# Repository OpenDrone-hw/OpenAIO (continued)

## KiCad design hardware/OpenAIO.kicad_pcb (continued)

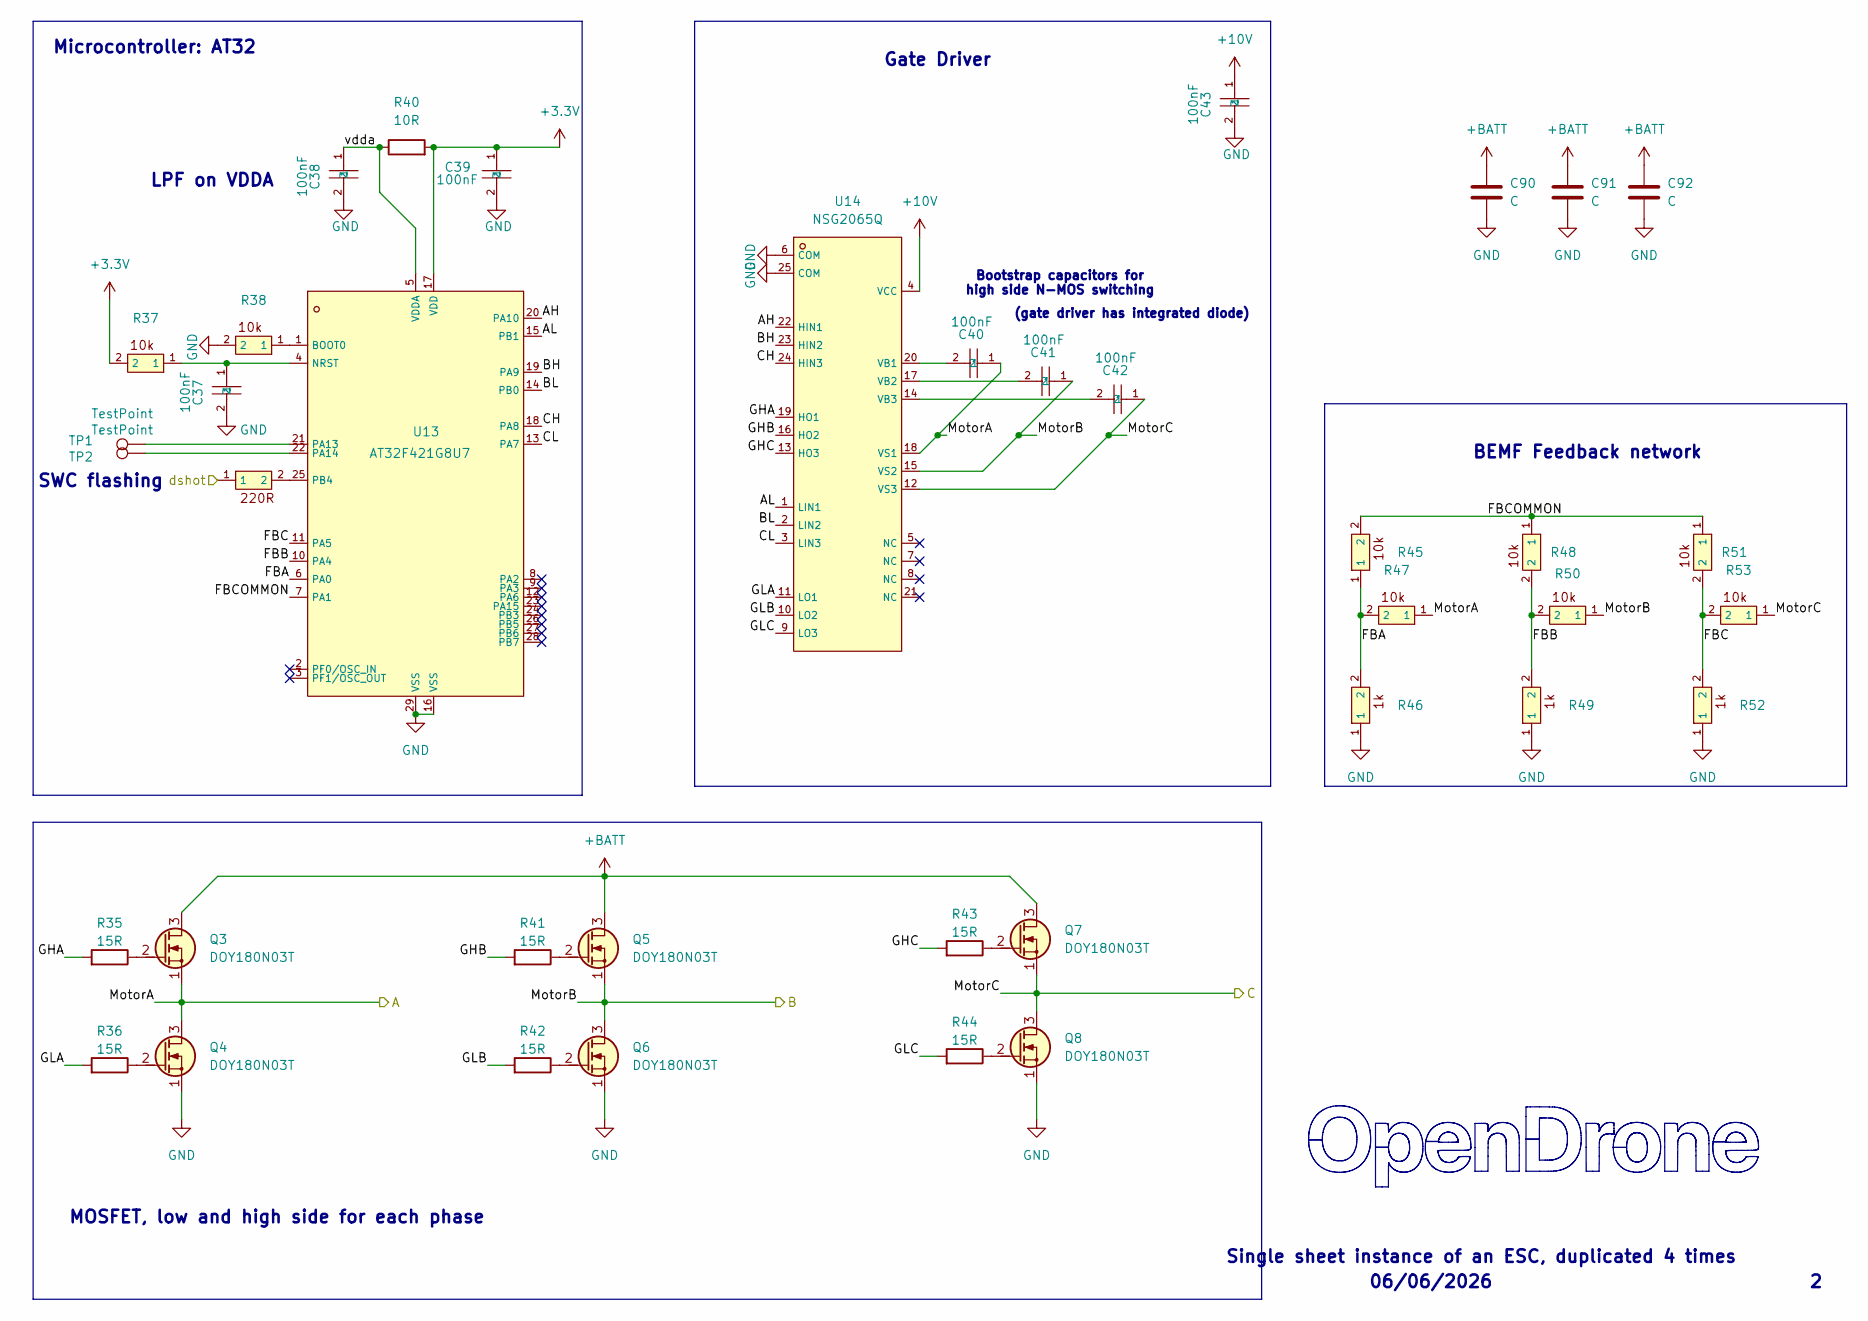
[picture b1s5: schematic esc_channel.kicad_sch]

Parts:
C37, C38, C39, C43: 100nF; C_0201_0603Metric; MPN GRM033R6YA104KE14D; LCSC C181043
C40, C41, C42: 100nF; C_0402_WIDE; MPN CL05B104KB54PNC; LCSC C307331
C90, C91, C92: C; C_0805_2012Metric
Q3, Q4, Q5, Q6, Q7, Q8: DOY180N03T; Diodes_PowerDI3333-8; MPN DOY180N03T; LCSC C49441966
R35, R36, R41, R42, R43, R44: 15R; R_0201_0603Metric; MPN 0201WMF150JTEE; LCSC C473542
R37, R38, R45, R47, R48, R50, R51, R53: 10k; R_0201_0603Metric; MPN RC0201FR-0710KL; LCSC C106225
R39: 220R; R_0201_0603Metric; MPN AC0201FR-07220RL; LCSC C226468
R40: 10R; R_0201_0603Metric; MPN RC0201FR-0710RL; LCSC C106226
R46, R49, R52: 1k; R_0201_0603Metric; MPN 0201WMF1001TEE; LCSC C270365
TP1, TP2: TestPoint; TestPoint_Pad_D1.0mm
U13: AT32F421G8U7; QFN-28_L4.0-W4.0-P0.40-TL-EP2.4; MPN AT32F421G8U7; LCSC C2765098
U14: NSG2065Q; QFN-24_L4.0-W4.0-P0.50-TL-EP2.8; MPN NSG2065Q; LCSC C41414478

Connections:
+3.3V: C39.1, R37.2, R40.2, U13.17 (VDD); also elsewhere on the board
+10V: C43.1, U14.4 (VCC); also elsewhere on the board
+BATT: C90.1, C91.1, C92.1, Q3.3 (D), Q5.3 (D), Q7.3 (D); also elsewhere on the board
/1A: C40.1, Q3.1 (S), Q4.3 (D), R47.1, U14.18 (VS1); also elsewhere on the board
/1B: C41.1, Q5.1 (S), Q6.3 (D), R50.1, U14.15 (VS2); also elsewhere on the board
/1C: C42.1, Q7.1 (S), Q8.3 (D), R53.1, U14.12 (VS3); also elsewhere on the board
/ESC1/AH: U13.20 (PA10), U14.22 (HIN1)
/ESC1/AL: U13.15 (PB1), U14.1 (LIN1)
/ESC1/BH: U13.19 (PA9), U14.23 (HIN2)
/ESC1/BL: U13.14 (PB0), U14.2 (LIN2)
/ESC1/CH: U13.18 (PA8), U14.24 (HIN3)
/ESC1/CL: U13.13 (PA7), U14.3 (LIN3)
/ESC1/FBA: R45.1, R46.2, R47.2, U13.6 (PA0)
/ESC1/FBB: R48.2, R49.2, R50.2, U13.10 (PA4)
/ESC1/FBC: R51.2, R52.2, R53.2, U13.11 (PA5)
/ESC1/FBCOMMON: R45.2, R48.1, R51.1, U13.7 (PA1)
/ESC1/GHA: R35.1, U14.19 (HO1)
/ESC1/GHB: R41.1, U14.16 (HO2)
/ESC1/GHC: R43.1, U14.13 (HO3)
/ESC1/GLA: R36.1, U14.11 (LO1)
/ESC1/GLB: R42.1, U14.10 (LO2)
/ESC1/GLC: R44.1, U14.9 (LO3)
/ESC1/vdda: C38.1, R40.1, U13.5 (VDDA)
GND: C37.2, C38.2, C39.2, C43.2, C90.2, C91.2, C92.2, Q4.1 (S), Q6.1 (S), Q8.1 (S), R38.2, R46.1, R49.1, R52.1, U13.16 (VSS), U13.29 (VSS), U14.6 (COM), U14.25 (COM); also elsewhere on the board
MOTOR1: R39.1; also elsewhere on the board
unnamed: Q3.2 (G), R35.2
unnamed: Q4.2 (G), R36.2
unnamed: Q5.2 (G), R41.2
unnamed: Q6.2 (G), R42.2
unnamed: Q7.2 (G), R43.2
unnamed: Q8.2 (G), R44.2
unnamed: R38.1, U13.1 (BOOT0)
unnamed: C37.1, R37.1, U13.4 (NRST)
unnamed: TP1.1 (1_1), U13.21 (PA13)
unnamed: TP2.1 (1_1), U13.22 (PA14)
unnamed: R39.2, U13.25 (PB4)
unnamed: C40.2, U14.20 (VB1)
unnamed: C41.2, U14.17 (VB2)
unnamed: C42.2, U14.14 (VB3)

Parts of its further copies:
C44, C45, C46, C48, C50, C51, C52, C57, C58, C60, C64: 100nF; C_0201_0603Metric; MPN GRM033R6YA104KE14D; LCSC C181043
C47, C49, C53, C54, C55, C56, C59, C61, C62, C63: 100nF; C_0402_WIDE; MPN CL05B104KB54PNC; LCSC C307331
C93, C94, C95, C96, C97, C98, C99, C100, C101: C; C_0805_2012Metric
Q9, Q10, Q11, Q12, Q13, Q14, Q15, Q16, Q17, Q18, Q19, Q20, Q21, Q22, Q23, Q24, Q25, Q26: DOY180N03T; Diodes_PowerDI3333-8; MPN DOY180N03T; LCSC C49441966
R55, R60, R61, R62, R63, R73, R79, R80, R81, R82, R92, R93, R98, R99, R100, R101: 15R; R_0201_0603Metric; MPN 0201WMF150JTEE; LCSC C473542
R56, R57, R64, R66, R67, R69, R70, R72, R75, R83, R85, R86, R88, R89, R91, R94, R95, R102, R104, R105, R107, R108, R110: 10k; R_0201_0603Metric; MPN RC0201FR-0710KL; LCSC C106225
R58, R77, R96: 220R; R_0201_0603Metric; MPN AC0201FR-07220RL; LCSC C226468
R65, R68, R71, R84, R87, R90, R103, R106, R109: 1k; R_0201_0603Metric; MPN 0201WMF1001TEE; LCSC C270365
R78, R97: 10R; R_0201_0603Metric; MPN RC0201FR-0710RL; LCSC C106226
TP3, TP4, TP5, TP6, TP7, TP8: TestPoint; TestPoint_Pad_D1.0mm
U15, U17, U19: AT32F421G8U7; QFN-28_L4.0-W4.0-P0.40-TL-EP2.4; MPN AT32F421G8U7; LCSC C2765098
U16, U18, U20: NSG2065Q; QFN-24_L4.0-W4.0-P0.50-TL-EP2.8; MPN NSG2065Q; LCSC C41414478

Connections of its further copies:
+3.3V: C46.1, C53.1, C60.1, R56.2, R75.2, R78.2, R94.2, R97.2, U15.17 (VDD), U17.17 (VDD), U19.17 (VDD); also elsewhere on the board
+10V: C50.1, C57.1, C64.1, U16.4 (VCC), U18.4 (VCC), U20.4 (VCC); also elsewhere on the board
+BATT: C93.1, C94.1, C95.1, C96.1, C97.1, C98.1, C99.1, C100.1, C101.1, Q9.3 (D), Q11.3 (D), Q13.3 (D), Q15.3 (D), Q17.3 (D), Q19.3 (D), Q21.3 (D), Q23.3 (D), Q25.3 (D); also elsewhere on the board
/2A: C47.1, Q9.1 (S), Q10.3 (D), R66.1, U16.18 (VS1); also elsewhere on the board
/2B: C48.1, Q11.1 (S), Q12.3 (D), R69.1, U16.15 (VS2); also elsewhere on the board
/2C: C49.1, Q13.1 (S), Q14.3 (D), R72.1, U16.12 (VS3); also elsewhere on the board
/3A: C54.1, Q15.1 (S), Q16.3 (D), R85.1, U18.18 (VS1); also elsewhere on the board
/3B: C55.1, Q17.1 (S), Q18.3 (D), R88.1, U18.15 (VS2); also elsewhere on the board
/3C: C56.1, Q19.1 (S), Q20.3 (D), R91.1, U18.12 (VS3); also elsewhere on the board
/4A: C61.1, Q21.1 (S), Q22.3 (D), R104.1, U20.18 (VS1); also elsewhere on the board
/4B: C62.1, Q23.1 (S), Q24.3 (D), R107.1, U20.15 (VS2); also elsewhere on the board
/4C: C63.1, Q25.1 (S), Q26.3 (D), R110.1, U20.12 (VS3); also elsewhere on the board
/ESC2/AH: U15.20 (PA10), U16.22 (HIN1)
/ESC2/AL: U15.15 (PB1), U16.1 (LIN1)
/ESC2/BH: U15.19 (PA9), U16.23 (HIN2)
/ESC2/BL: U15.14 (PB0), U16.2 (LIN2)
/ESC2/CH: U15.18 (PA8), U16.24 (HIN3)
/ESC2/CL: U15.13 (PA7), U16.3 (LIN3)
/ESC2/FBA: R64.1, R65.2, R66.2, U15.6 (PA0)
/ESC2/FBB: R67.2, R68.2, R69.2, U15.10 (PA4)
/ESC2/FBC: R70.2, R71.2, R72.2, U15.11 (PA5)
/ESC2/FBCOMMON: R64.2, R67.1, R70.1, U15.7 (PA1)
/ESC2/GHA: U16.19 (HO1); also elsewhere on the board
/ESC2/GHB: R60.1, U16.16 (HO2)
/ESC2/GHC: R62.1, U16.13 (HO3)
/ESC2/GLA: R55.1, U16.11 (LO1)
/ESC2/GLB: R61.1, U16.10 (LO2)
/ESC2/GLC: R63.1, U16.9 (LO3)
/ESC2/vdda: C45.1, U15.5 (VDDA); also elsewhere on the board
/ESC3/AH: U17.20 (PA10), U18.22 (HIN1)
/ESC3/AL: U17.15 (PB1), U18.1 (LIN1)
/ESC3/BH: U17.19 (PA9), U18.23 (HIN2)
/ESC3/BL: U17.14 (PB0), U18.2 (LIN2)
/ESC3/CH: U17.18 (PA8), U18.24 (HIN3)
/ESC3/CL: U17.13 (PA7), U18.3 (LIN3)
/ESC3/FBA: R83.1, R84.2, R85.2, U17.6 (PA0)
/ESC3/FBB: R86.2, R87.2, R88.2, U17.10 (PA4)
/ESC3/FBC: R89.2, R90.2, R91.2, U17.11 (PA5)
/ESC3/FBCOMMON: R83.2, R86.1, R89.1, U17.7 (PA1)
/ESC3/GHA: R73.1, U18.19 (HO1)
/ESC3/GHB: R79.1, U18.16 (HO2)
/ESC3/GHC: R81.1, U18.13 (HO3)
/ESC3/GLA: U18.11 (LO1); also elsewhere on the board
/ESC3/GLB: R80.1, U18.10 (LO2)
/ESC3/GLC: R82.1, U18.9 (LO3)
/ESC3/vdda: C52.1, R78.1, U17.5 (VDDA)
/ESC4/AH: U19.20 (PA10), U20.22 (HIN1)
/ESC4/AL: U19.15 (PB1), U20.1 (LIN1)
/ESC4/BH: U19.19 (PA9), U20.23 (HIN2)
/ESC4/BL: U19.14 (PB0), U20.2 (LIN2)
/ESC4/CH: U19.18 (PA8), U20.24 (HIN3)
/ESC4/CL: U19.13 (PA7), U20.3 (LIN3)
/ESC4/FBA: R102.1, R103.2, R104.2, U19.6 (PA0)
/ESC4/FBB: R105.2, R106.2, R107.2, U19.10 (PA4)
/ESC4/FBC: R108.2, R109.2, R110.2, U19.11 (PA5)
/ESC4/FBCOMMON: R102.2, R105.1, R108.1, U19.7 (PA1)
/ESC4/GHA: R92.1, U20.19 (HO1)
/ESC4/GHB: R98.1, U20.16 (HO2)
/ESC4/GHC: R100.1, U20.13 (HO3)
/ESC4/GLA: R93.1, U20.11 (LO1)
/ESC4/GLB: R99.1, U20.10 (LO2)
/ESC4/GLC: R101.1, U20.9 (LO3)
/ESC4/vdda: C59.1, R97.1, U19.5 (VDDA)
GND: C44.2, C45.2, C46.2, C50.2, C51.2, C52.2, C53.2, C57.2, C58.2, C59.2, C60.2, C64.2, C93.2, C94.2, C95.2, C96.2, C97.2, C98.2, C99.2, C100.2, C101.2, Q10.1 (S), Q12.1 (S), Q14.1 (S), Q16.1 (S), Q18.1 (S), Q20.1 (S), Q22.1 (S), Q24.1 (S), Q26.1 (S), R57.2, R65.1, R68.1, R71.1, R84.1, R87.1, R90.1, R95.2, R103.1, R106.1, R109.1, U15.16 (VSS), U15.29 (VSS), U16.6 (COM), U16.25 (COM), U17.16 (VSS), U17.29 (VSS), U18.6 (COM), U18.25 (COM), U19.16 (VSS), U19.29 (VSS), U20.6 (COM), U20.25 (COM); also elsewhere on the board
MOTOR2: R58.1; also elsewhere on the board
MOTOR3: R77.1; also elsewhere on the board
MOTOR4: R96.1; also elsewhere on the board
unnamed 154: Q9.2 (G); also elsewhere on the board
unnamed: Q10.2 (G), R55.2
unnamed: Q11.2 (G), R60.2
unnamed: Q12.2 (G), R61.2
unnamed: Q13.2 (G), R62.2
unnamed: Q14.2 (G), R63.2
unnamed: Q15.2 (G), R73.2
unnamed 161: Q16.2 (G); also elsewhere on the board
unnamed: Q17.2 (G), R79.2
unnamed: Q18.2 (G), R80.2
unnamed: Q19.2 (G), R81.2
unnamed: Q20.2 (G), R82.2
unnamed: Q21.2 (G), R92.2
unnamed: Q22.2 (G), R93.2
unnamed: Q23.2 (G), R98.2
unnamed: Q24.2 (G), R99.2
unnamed: Q25.2 (G), R100.2
unnamed: Q26.2 (G), R101.2
unnamed: R57.1, U15.1 (BOOT0)
unnamed: C44.1, R56.1, U15.4 (NRST)
unnamed: TP3.1 (1_1), U15.21 (PA13)
unnamed: TP4.1 (1_1), U15.22 (PA14)
unnamed: R58.2, U15.25 (PB4)
unnamed: C47.2, U16.20 (VB1)
unnamed: C48.2, U16.17 (VB2)
unnamed: C49.2, U16.14 (VB3)
unnamed 204: U17.1 (BOOT0); also elsewhere on the board
unnamed: C51.1, R75.1, U17.4 (NRST)
unnamed: TP5.1 (1_1), U17.21 (PA13)
unnamed: TP6.1 (1_1), U17.22 (PA14)
unnamed: R77.2, U17.25 (PB4)
unnamed: C54.2, U18.20 (VB1)
unnamed: C55.2, U18.17 (VB2)
unnamed: C56.2, U18.14 (VB3)
unnamed: R95.1, U19.1 (BOOT0)
unnamed: C58.1, R94.1, U19.4 (NRST)
unnamed: TP7.1 (1_1), U19.21 (PA13)
unnamed: TP8.1 (1_1), U19.22 (PA14)
unnamed: R96.2, U19.25 (PB4)
unnamed: C61.2, U20.20 (VB1)
unnamed: C62.2, U20.17 (VB2)
unnamed: C63.2, U20.14 (VB3)

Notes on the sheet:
Bootstrap capacitors for high side N-MOS switching
Gate Driver
MOSFET, low and high side for each phase
Single sheet instance of an ESC, duplicated 4 times
Microcontroller: AT32
SWC flashing
(gate driver has integrated diode)
06/06/2026
BEMF Feedback network
LPF on VDDA

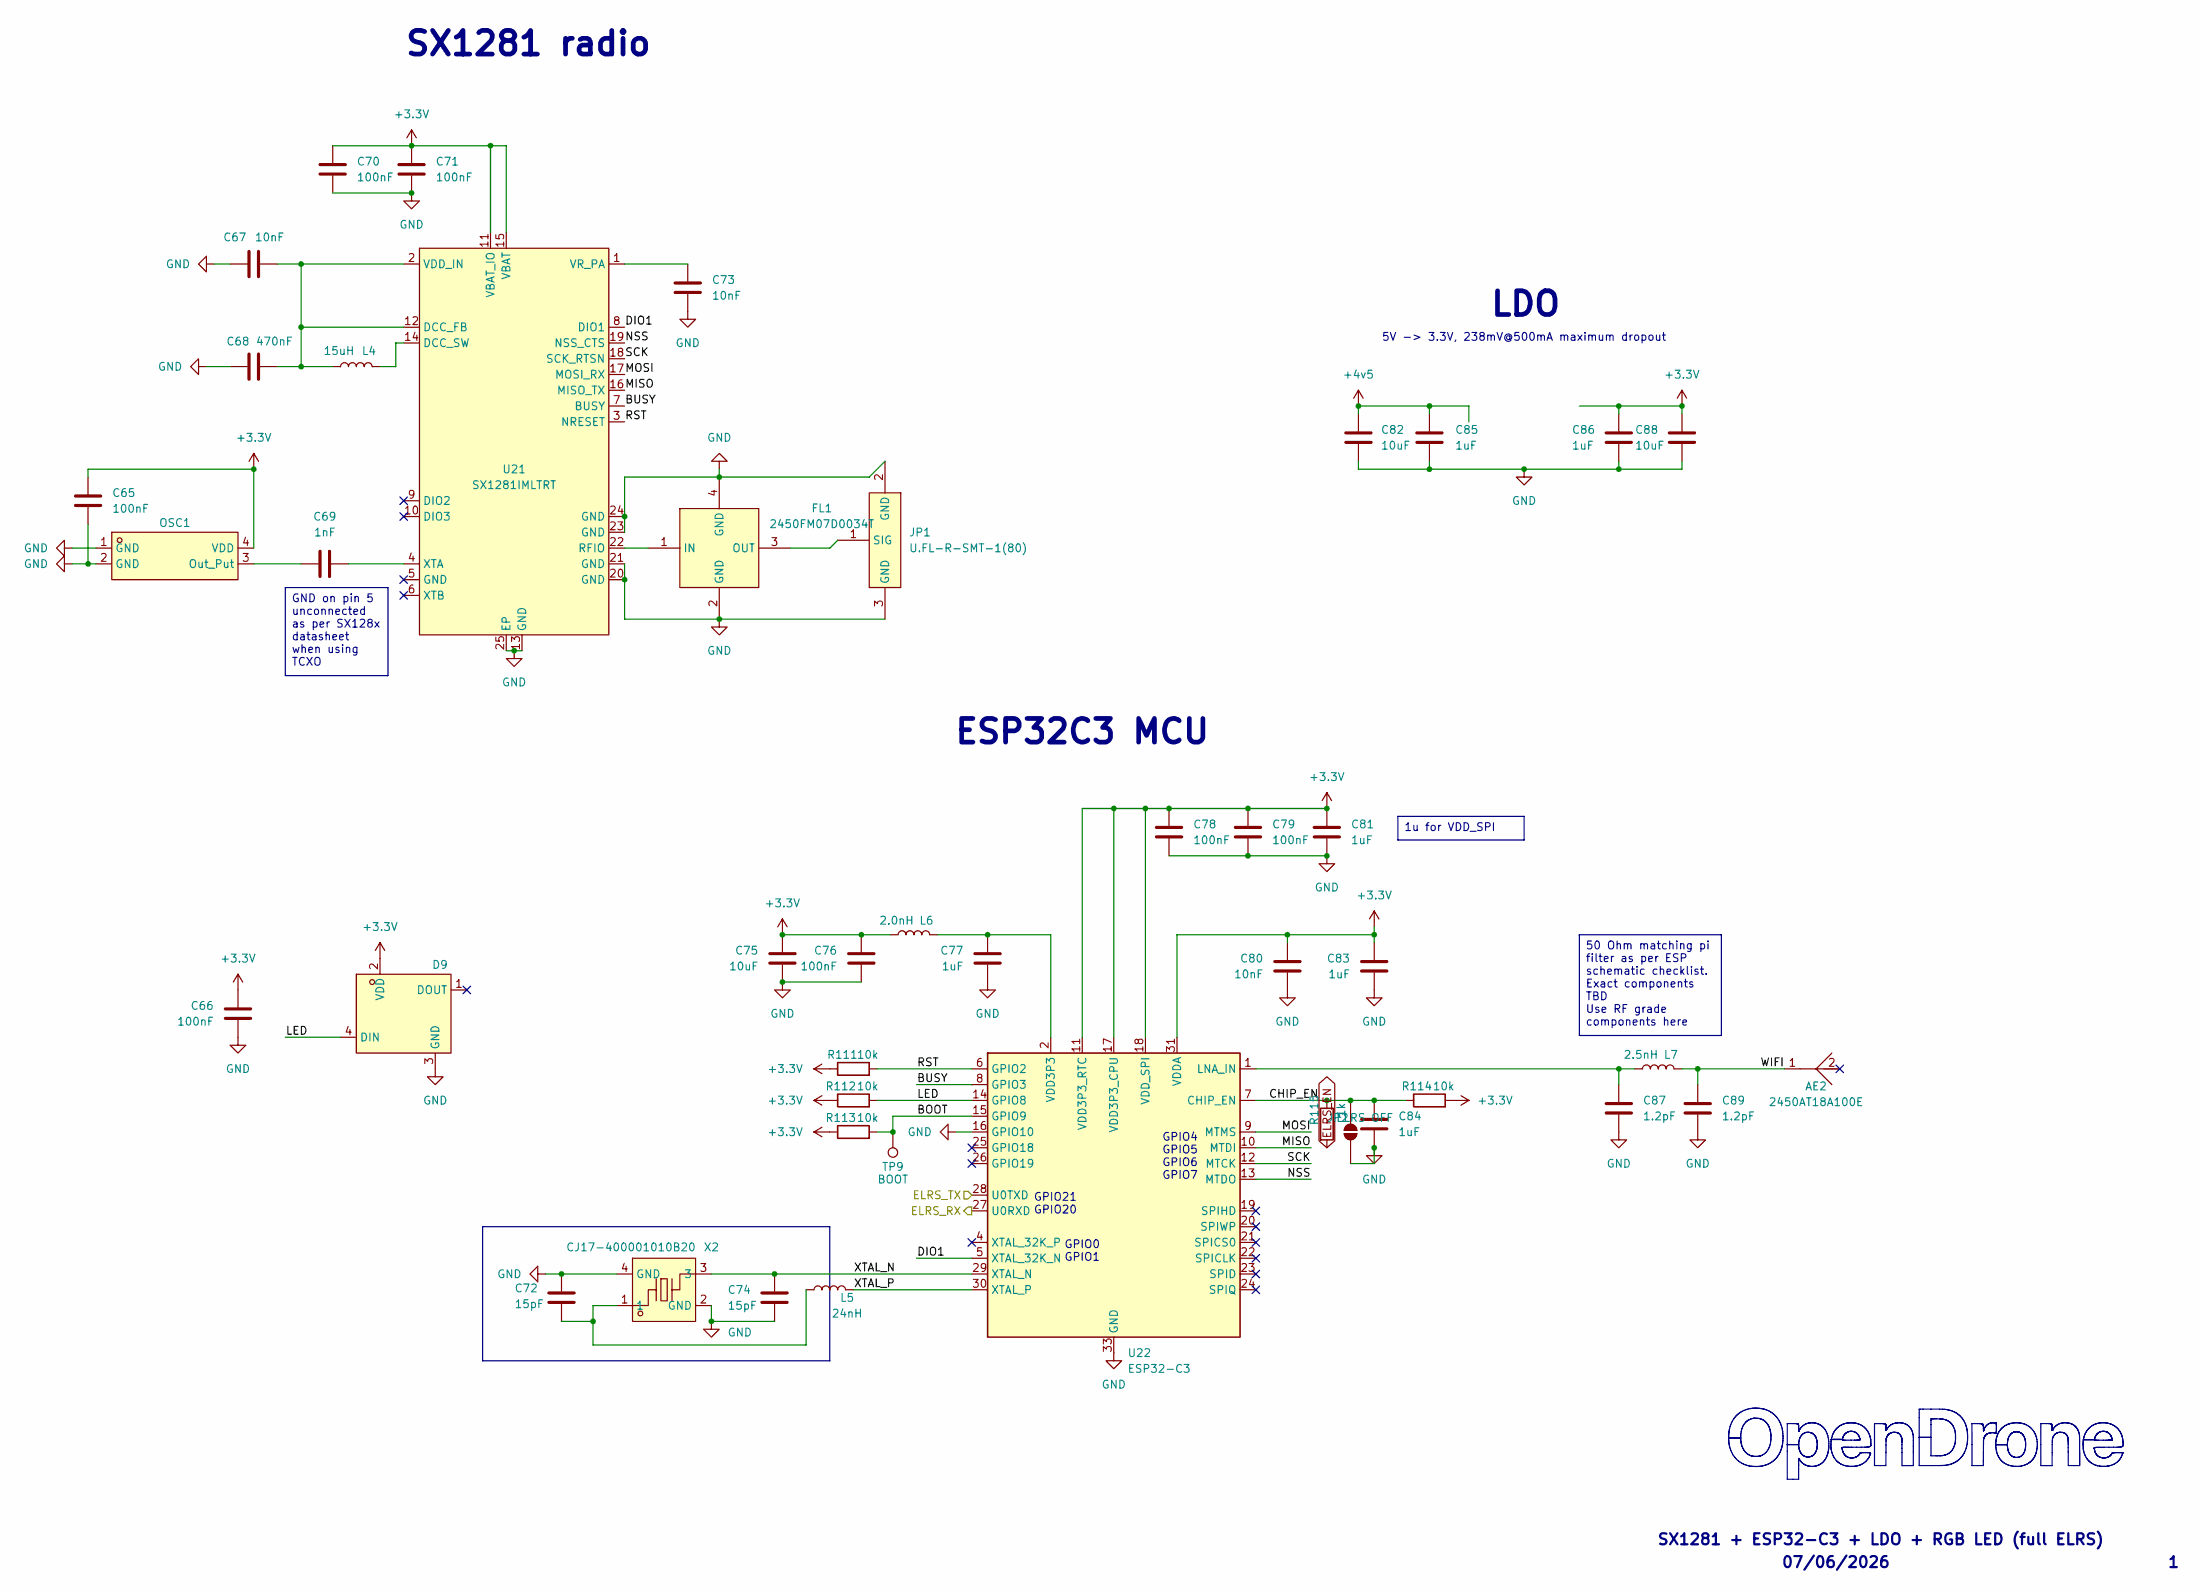
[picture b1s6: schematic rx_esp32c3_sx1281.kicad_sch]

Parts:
AE2: 2450AT18A100E; ANT-SMD_L3.2-W1.6; LCSC Part C89334
C65, C66, C70, C71, C76, C78, C79: 100nF; C_0201_0603Metric; LCSC C76939
C67, C73, C80: 10nF; C_0201_0603Metric; LCSC C2168164
C68: 470nF; C_0201_0603Metric; LCSC C85926
C69: 1nF; C_0201_0603Metric; LCSC C66942
C72, C74: 15pF; C_0201_0603Metric; LCSC C85891
C75: 10uF; C_0402_1005Metric; LCSC C76991
C77, C81, C83, C84, C85, C86: 1uF; C_0201_0603Metric; LCSC C76935
C82, C88: 10uF; C_0402_1005Metric; LCSC C15525
C87, C89: 1.2pF; C_0201_0603Metric; LCSC C85895
D9: XL-1010RGBC-WS2812B; LED-SMD_4P-L1.0-W1.0-TL_XL-1010RGBC-WS2812B; LCSC Part C5349953
FL1: 2450FM07D0034T; FILTER-SMD_4P-L1.0-W0.5-L; MPN 2450FM07D0034T; LCSC Part C2651081
JP1: U.FL-R-SMT-1(80); RF-SMD_FRF05002-JSS103M; LCSC Part C88374
JP2: ELRS OFF; SolderJumper-2_P0.65mm_Tiny_Open
L4: 15uH; L_0805_2012Metric
L5: 24nH; L_0201_0603Metric; LCSC C206441
L6: 2.0nH; L_0201_0603Metric; LCSC C86125
L7: 2.5nH; L_0201_0603Metric; LCSC C206435
OSC1: OW7EL89CENUNFAYLC-52M; OSC-SMD_4P-L2.0-W1.6-BL_TXC_7Z; LCSC Part C22434896
R111, R112, R113, R114: 10k; R_0201_0603Metric; LCSC C106225
R115: 1k; R_0201_0603Metric
TP9: BOOT; SolderPad_1.2x2.0mm
U21: SX1281IMLTRT; QFN-24_L4.0-W4.0-P0.50-TL-EP2.6; LCSC Part C2151551
U22: ESP32-C3; QFN-32-1EP_5x5mm_P0.5mm_EP3.7x3.7mm
X2: CJ17-400001010B20; CRYSTAL-SMD_4P-L1.6-W1.2-BL; LCSC Part C2875272

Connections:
+3.3V: C65.1, C66.1, C70.1, C71.1, C75.1, C76.1, C78.1, C79.1, C80.1, C81.1, C83.1, C86.1, C88.1, D9.2 (VDD), L6.2, OSC1.4 (VDD), R111.1, R112.1, R113.1, R114.2, U21.11 (VBAT_IO), U21.15 (VBAT), U22.11 (VDD3P3_RTC), U22.17 (VDD3P3_CPU), U22.18 (VDD_SPI), U22.31 (VDDA), U22.32 (VDDA); also elsewhere on the board
+4v5: C82.1, C85.1; also elsewhere on the board
/RX/BOOT: R113.2, TP9.1 (1_1), U22.15 (GPIO9)
/RX/BUSY: U21.7 (BUSY), U22.8 (GPIO3)
/RX/CHIP_EN: C84.1, JP2.2 (B), R114.1, R115.1, U22.7 (CHIP_EN)
/RX/DIO1: U21.8 (DIO1), U22.5 (XTAL_32K_N)
/RX/LED: D9.4 (DIN), R112.2, U22.14 (GPIO8)
/RX/MISO: U21.16 (MISO_TX), U22.10 (MTDI)
/RX/MOSI: U21.17 (MOSI_RX), U22.9 (MTMS)
/RX/NSS: U21.19 (NSS_CTS), U22.13 (MTDO)
/RX/RST: R111.2, U21.3 (NRESET), U22.6 (GPIO2)
/RX/SCK: U21.18 (SCK_RTSN), U22.12 (MTCK)
/RX/WIFI: AE2.1, C89.1, L7.1
/RX/XTAL_N: C74.1, U22.29 (XTAL_N), X2.3
/RX/XTAL_P: L5.2, U22.30 (XTAL_P)
ELRS_EN: R115.2; also elsewhere on the board
GND: C65.2, C66.2, C67.1, C68.1, C70.2, C71.2, C72.2, C73.2, C74.2, C75.2, C76.2, C77.2, C78.2, C79.2, C80.2, C81.2, C82.2, C83.2, C84.2, C85.2, C86.2, C87.2, C88.2, C89.2, D9.3 (GND), FL1.2 (GND), FL1.4 (GND), JP1.2 (GND), JP1.3 (GND), JP2.1 (A), OSC1.1 (GND), OSC1.2 (GND), U21.13 (GND), U21.20 (GND), U21.21 (GND), U21.23 (GND), U21.24 (GND), U21.25 (EP), U22.16 (GPIO10), U22.33 (GND), X2.2 (GND), X2.4 (GND); also elsewhere on the board
unnamed: C72.1, L5.1, X2.1
unnamed: C77.1, L6.1, U22.2 (VDD3P3), U22.3 (VDD3P3)
unnamed: FL1.1 (IN), U21.22 (RFIO)
unnamed: FL1.3 (OUT), JP1.1 (SIG)
unnamed: C69.1, OSC1.3 (Out_Put)
unnamed: C67.2, C68.2, L4.1, U21.2 (VDD_IN), U21.12 (DCC_FB)
unnamed: L4.2, U21.14 (DCC_SW)
unnamed: C73.1, U21.1 (VR_PA)
unnamed: C69.2, U21.4 (XTA)
unnamed: C87.1, L7.2, U22.1 (LNA_IN)
UART1_RX: U22.28 (U0TXD); also elsewhere on the board
UART1_TX: U22.27 (U0RXD); also elsewhere on the board

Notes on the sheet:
5V -> 3.3V, 238mV@500mA maximum dropout
GPIO0 GPIO1
SX1281 + ESP32-C3 + LDO + RGB LED (full ELRS)
GPIO21 GPIO20
GPIO4 GPIO5 GPIO6 GPIO7
SX1281 radio
LDO
ESP32C3 MCU
07/06/2026
GND on pin 5 unconnected as per SX128x datasheet when using TCXO
1u for VDD_SPI
50 Ohm matching pi filter as per ESP schematic checklist. Exact components TBD Use RF grade components here

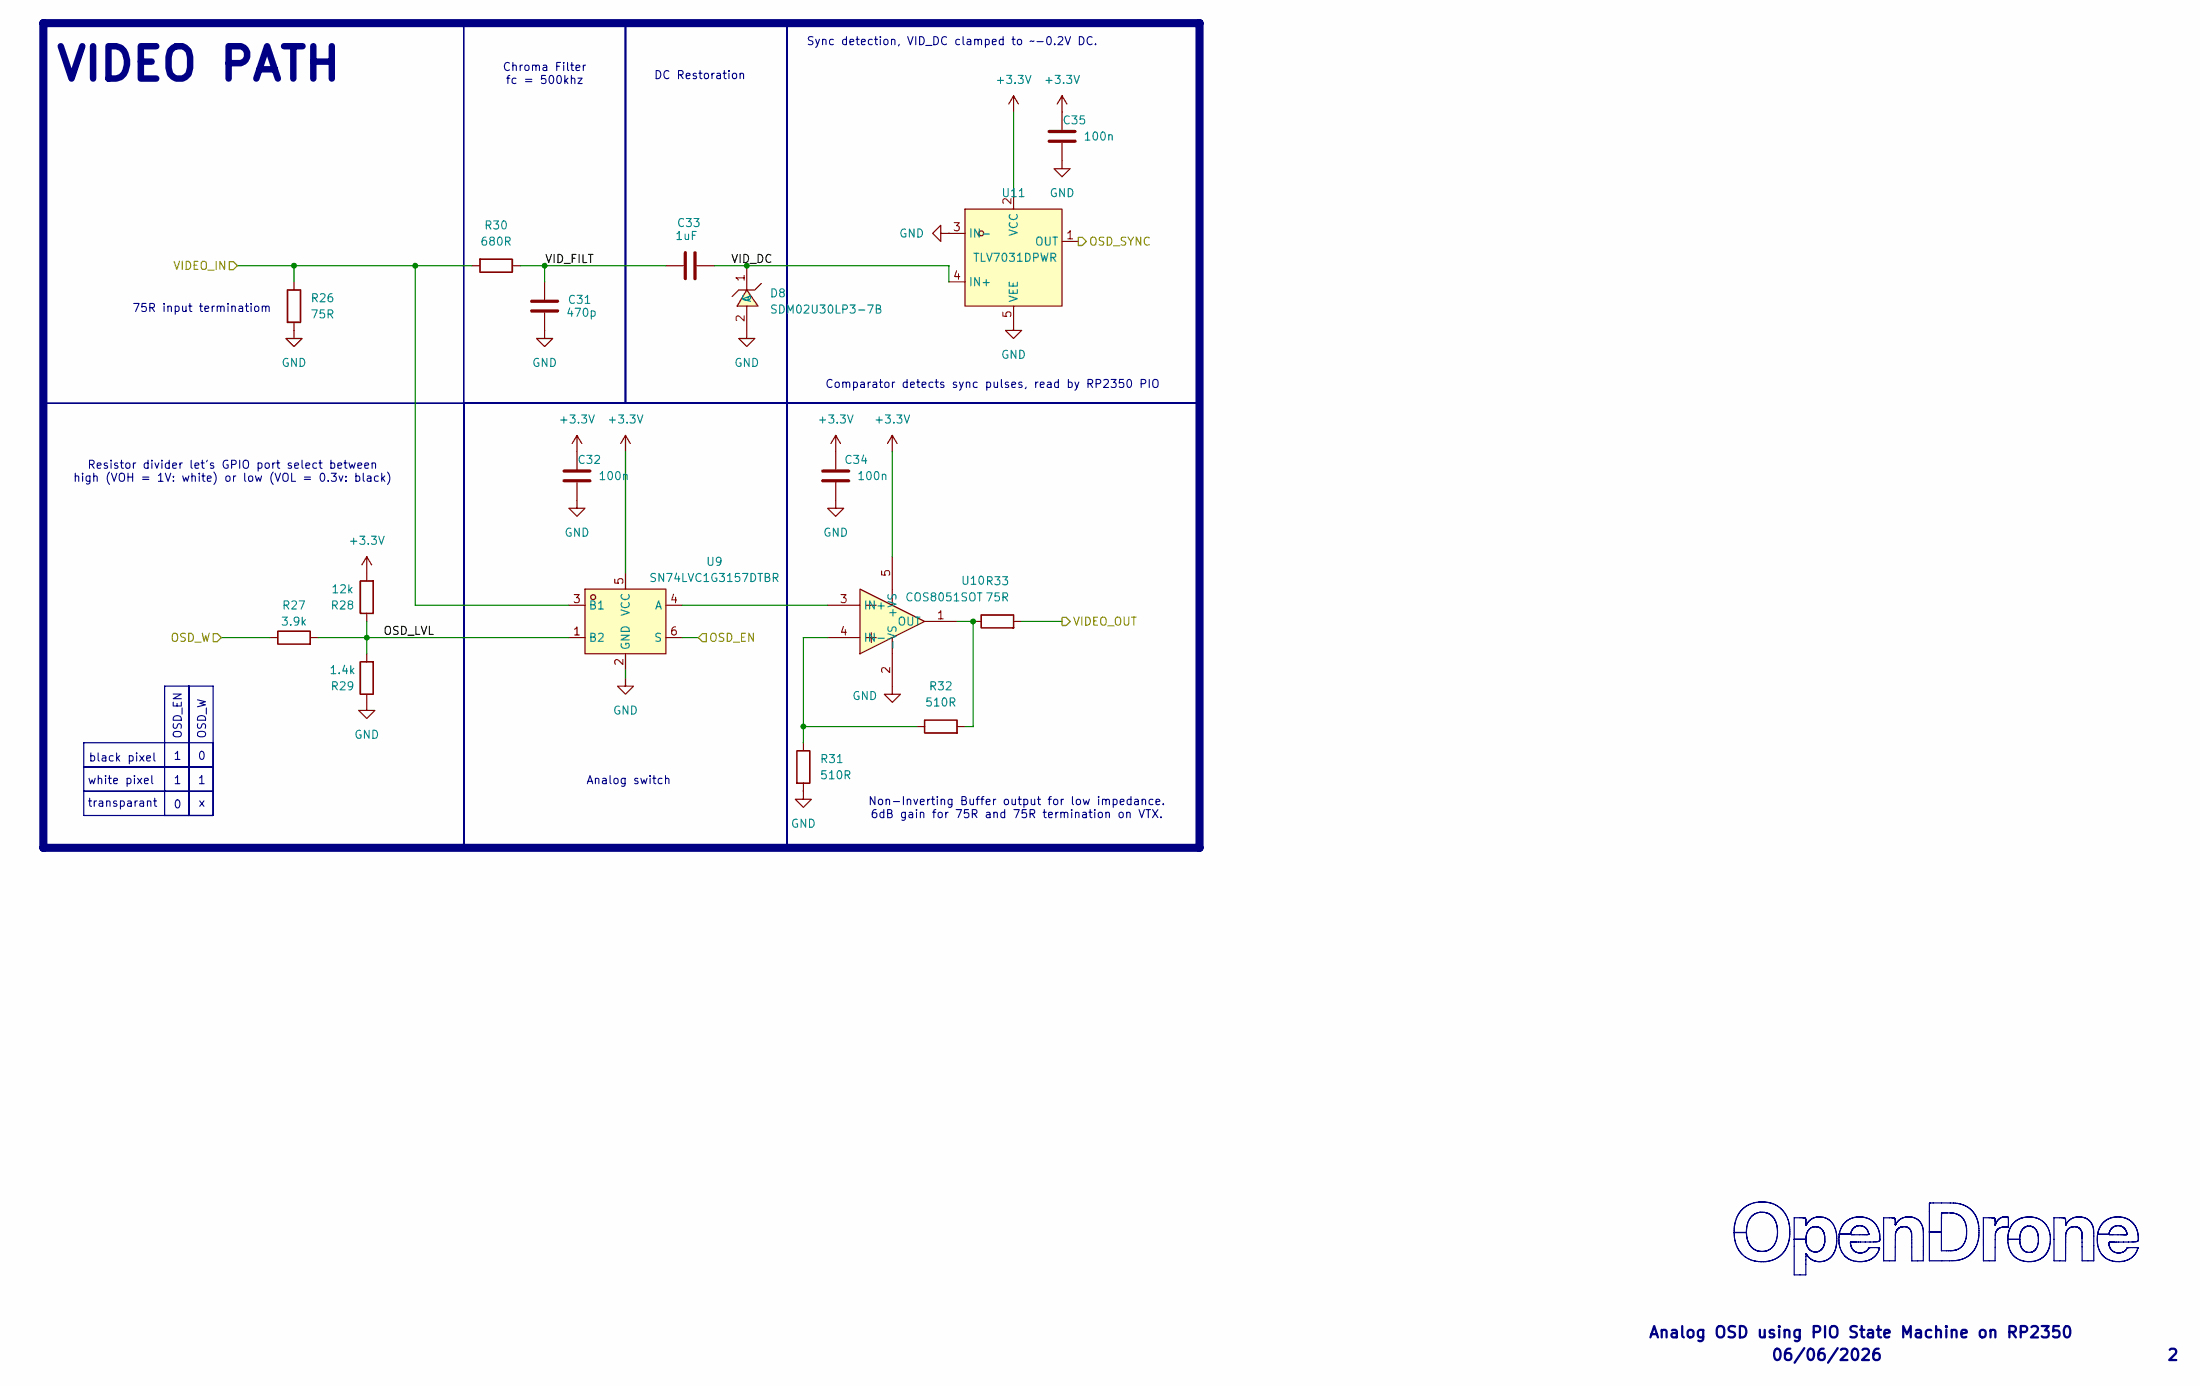
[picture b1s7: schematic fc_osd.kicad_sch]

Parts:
C31: 470p; C_0201_0603Metric; MPN CC0201JRX7R9BB471; LCSC C526944
C32, C34, C35: 100n; C_0201_0603Metric; MPN GRM033R60J104KE19D; LCSC C76928
C33: 1uF; C_0402_1005Metric; MPN CL05A105KA5NQNC; LCSC C52923
D8: SDM02U30LP3-7B; X3-DFN0603-2_L0.6-W0.3-RD; MPN SDM02U30LP3-7B; LCSC C151629
R26, R33: 75R; R_0201_0603Metric; MPN RC0201FR-0775RL; LCSC C274878
R27: 3.9k; R_0201_0603Metric; MPN RC0201FR-073K9L; LCSC C273280
R28: 12k; R_0201_0603Metric; MPN 0201WMF1202TEE; LCSC C270363
R29: 1.4k; R_0201_0603Metric; MPN 0201WMF1401TEE; LCSC C423739
R30: 680R; R_0201_0603Metric; MPN 0201WMF6800TEE; LCSC C473509
R31, R32: 510R; R_0201_0603Metric; LCSC C57784
U9: SN74LVC1G3157DTBR; X2SON-6_L1.0-W0.8-BL; MPN SN74LVC1G3157DTBR; LCSC C2673087
U10: COS8051SOT; SOT-23-5_L3.0-W1.7-P0.95-LS2.8-BR; MPN COS8051SOT; LCSC C7463385
U11: TLV7031DPWR; X2SON-4_L0.8-W0.8-P0.48-TL-A; MPN TLV7031DPWR; LCSC C2876045

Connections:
+3.3V: C32.1, C34.1, C35.1, R28.2, U9.5 (VCC), U10.5 (+VS), U11.2 (VCC); also elsewhere on the board
/OSD/OSD_EN: U9.6 (S); also elsewhere on the board
/OSD/OSD_LVL: R27.2, R28.1, R29.2, U9.1 (B2)
/OSD/OSD_SYNC: U11.1 (OUT); also elsewhere on the board
/OSD/OSD_W: R27.1; also elsewhere on the board
/OSD/VIDEO_IN: R26.1, R30.2, U9.3 (B1); also elsewhere on the board
/OSD/VIDEO_OUT: R33.2; also elsewhere on the board
/OSD/VID_DC: C33.2, D8.1 (C), U11.4 (IN+)
/OSD/VID_FILT: C31.1, C33.1, R30.1
GND: C31.2, C32.2, C34.2, C35.2, D8.2 (A), R26.2, R29.1, R31.2, U9.2 (GND), U10.2 (-VS), U11.3 (IN-), U11.5 (VEE); also elsewhere on the board
unnamed: U9.4 (A), U10.3 (IN+)
unnamed: R31.1, R32.1, U10.4 (IN-)
unnamed: R32.2, R33.1, U10.1 (OUT)

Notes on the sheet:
Sync detection, VID_DC clamped to ~-0.2V DC.
Non-Inverting Buffer output for low impedance. 6dB gain for 75R and 75R termination on VTX.
VIDEO PATH
06/06/2026
Analog switch
black pixel
white pixel
OSD_W
75R input terminatiom
Resistor divider let's GPIO port select between high (VOH = 1V: white) or low (VOL = 0.3v: black)
DC Restoration
Chroma Filter fc = 500khz
OSD_EN
transparant
Analog OSD using PIO State Machine on RP2350
Comparator detects sync pulses, read by RP2350 PIO

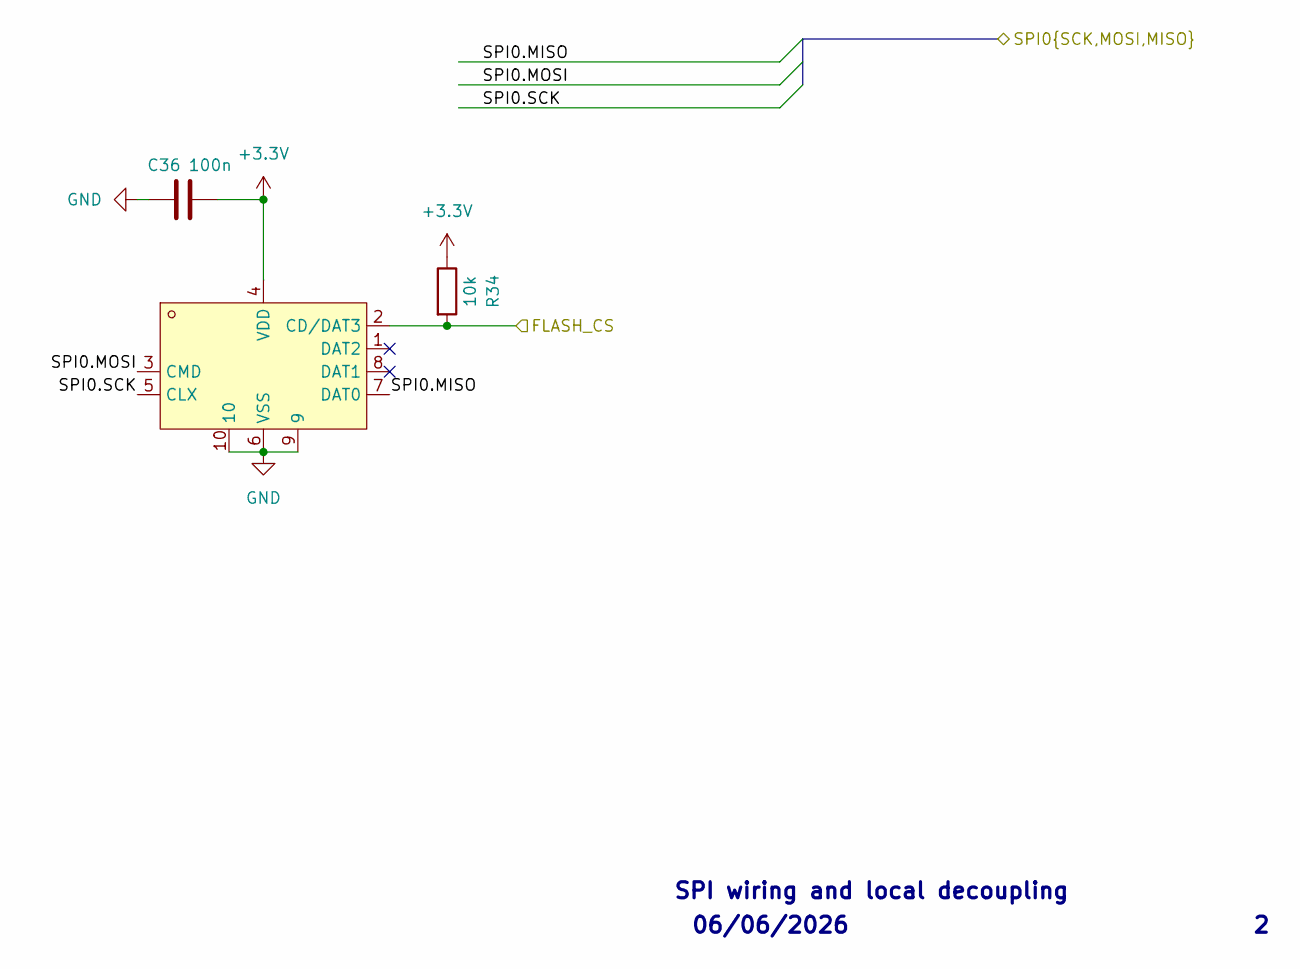
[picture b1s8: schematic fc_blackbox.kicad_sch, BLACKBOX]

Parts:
C36: 100n; C_0201_0603Metric; MPN GRM033R61E104KE14D; LCSC C76939
Card1: TF-021B-H265; TF-SMD_TF-021B-H265; LCSC C498185
R34: 10k; R_0201_0603Metric; MPN RC0201FR-0710KL; LCSC C106225

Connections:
+3.3V: C36.1, Card1.4 (VDD), R34.1; also elsewhere on the board
FLASH_CS: Card1.2 (CD/DAT3), R34.2; also elsewhere on the board
GND: C36.2, Card1.6 (VSS), Card1.9, Card1.10; also elsewhere on the board
SPI0.MISO: Card1.7 (DAT0); also elsewhere on the board
SPI0.MOSI: Card1.3 (CMD); also elsewhere on the board
SPI0.SCK: Card1.5 (CLX); also elsewhere on the board

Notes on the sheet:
SPI wiring and local decoupling
06/06/2026

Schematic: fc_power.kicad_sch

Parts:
C18, C19: 4.7uF 50v; C_0805_2012Metric; MPN CL21A475KBQNNNE; LCSC C98192
C20, C21, C26: 100n; C_0201_0603Metric; MPN GRM033R61E104KE14D; LCSC C76939
C23, C24: 22uF; C_0603_1608Metric; MPN CL10A226MO7JZNC; LCSC C2762594
C25: 4.7uF; C_0402_1005Metric; MPN CL05A475MP5NRNC; LCSC C23733
C27, C28: 22uF; C_0402_1005Metric; MPN GRM155R60J226ME11D; LCSC C415703
C102, C103: C; C_0805_2012Metric
C105, C106: C; C_1206_3216Metric
D2, D3: DSK24; SOD-123_L2.8-W1.8-LS3.7-RD; MPN DSK24; LCSC C64890
D4, D5, D6, D7: LED_1_Green; LED_0402_1005Metric; MPN XL-1005UGC; LCSC C965793
L2, L3: XRTC303020D4R7MBCA; IND-SMD_L3.0-W3.0_AFE303020S; MPN XRTC303020D4R7MBCA; LCSC C39846837
R17, R19: 100k; R_0201_0603Metric; MPN 0201WMF1003TEE; LCSC C270364
R18, R23: 6.49k; R_0201_0603Metric; LCSC C2107920
R20: 13.7k; R_0201_0603Metric; MPN RC-01W1372FT; LCSC C320695
R21: 7.5k; R_0201_0603Metric; LCSC C474437
R22: 2.4k; R_0201_0603Metric; LCSC C166281
R24: 510R; R_0201_0603Metric; LCSC C57784
TP30: TestPoint; TestPoint_Pad_D1.0mm
U3, U4: LMR51430YFDDCR; SOT-23-6_L2.9-W1.6-P0.95-LS2.9-BL; MPN LMR51430YFDDCR; LCSC C5219261
U6: LP5912-1.8DRVR; WSON-6-1EP_2x2mm_P0.65mm_EP1x1.6mm_ThermalVias; MPN LP5912-1.8DRVR; LCSC C2876234
U7: TLV76733DRVR; WSON-6-1EP_2x2mm_P0.65mm_EP1x1.6mm; MPN TLV76733DRVR; LCSC C2848334

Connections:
+1.8V_GYRO: C27.1, U6.1 (OUT); also elsewhere on the board
+3.3V: C28.1, R24.1, U7.1 (OUT), U7.2 (SNS); also elsewhere on the board
+4v5: C25.1, C26.1, D2.1 (K), D3.1 (K), R23.1, U6.4 (EN), U6.6 (IN), U7.4 (EN), U7.6 (IN); also elsewhere on the board
+5V: C24.1, D2.2 (A), L3.2, R19.2, R22.1, TP30.1; also elsewhere on the board
+5V_USB: D3.2 (A); also elsewhere on the board
+10V: C23.1, L2.2, R17.2, R21.1; also elsewhere on the board
+BATT: C18.1, C19.1, C102.1, C103.1, C105.1, C106.1, U3.3 (VIN), U3.5 (EN), U4.3 (VIN), U4.5 (EN); also elsewhere on the board
/Power/1.8V_PG: D7.2 (A), R23.2, U6.3 (PG)
GND: C18.2, C19.2, C23.2, C24.2, C25.2, C26.2, C27.2, C28.2, C102.2, C103.2, C105.2, C106.2, D4.1 (K), D5.1 (K), D6.1 (K), D7.1 (K), R18.2, R20.2, U3.1 (GND), U4.1 (GND), U6.5 (GND), U6.7 (EP), U7.3 (GND), U7.5 (GND), U7.7 (EP); also elsewhere on the board
unnamed: D4.2 (A), R21.2
unnamed: D5.2 (A), R22.2
unnamed: D6.2 (A), R24.2
unnamed: C20.2, U3.6 (CB)
unnamed: R17.1, R18.1, U3.4 (FB)
unnamed: C20.1, L2.1, U3.2 (SW)
unnamed: C21.2, U4.6 (CB)
unnamed: R19.1, R20.1, U4.4 (FB)
unnamed: C21.1, L3.1, U4.2 (SW)

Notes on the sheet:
Vout = Vref × (1 + R_top / R_bottom) = 0.6 × (1 + 100 / 13.7) = 0.6 × 8.299 = 4.980 V
1.8V LDO for IMU (high PSRR)
4.5 - 36V input Synchronous buck 1.1MHz
5V Power MUX
10V (3A)
3.3V 0.5A MAIN LDO
Up to 6.5V input (5V) Thermal Protection Short circuit protection Reverse current protection Low noise for RF and analog circuits
Vout = Vref × (1 + R_top / R_bottom) = 0.6 × (1 + 100 / 6.49) = 0.6 × 16.408 = 9.845 V
06/06/2026
FPWM version of the LMR51430 for less output ripple at low voltage and more consistency but less efficient
5V (3A)
LMR51430 = 3A output LMR51420 = 2A output (pin compatible)
Power delivery circuitry for flight controller

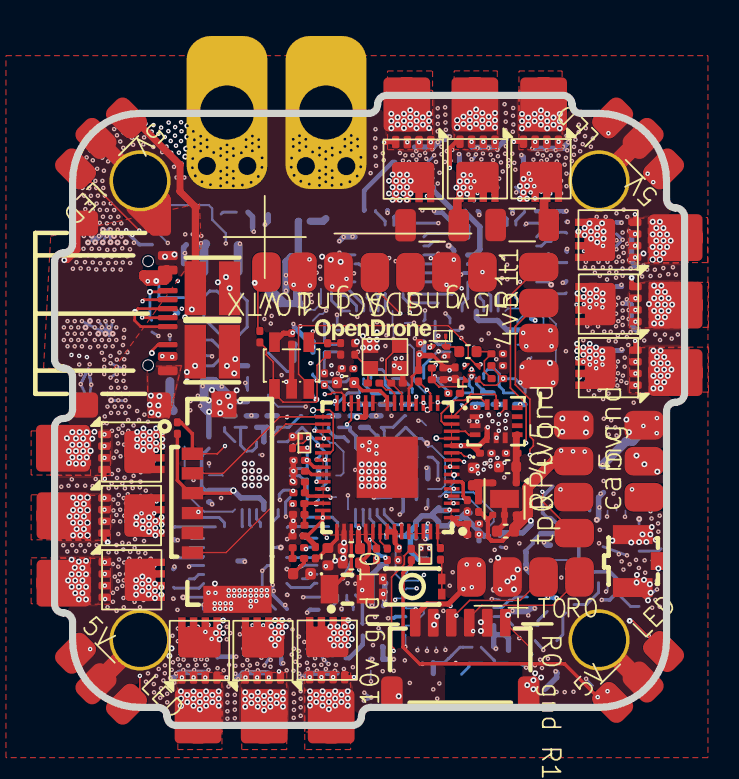
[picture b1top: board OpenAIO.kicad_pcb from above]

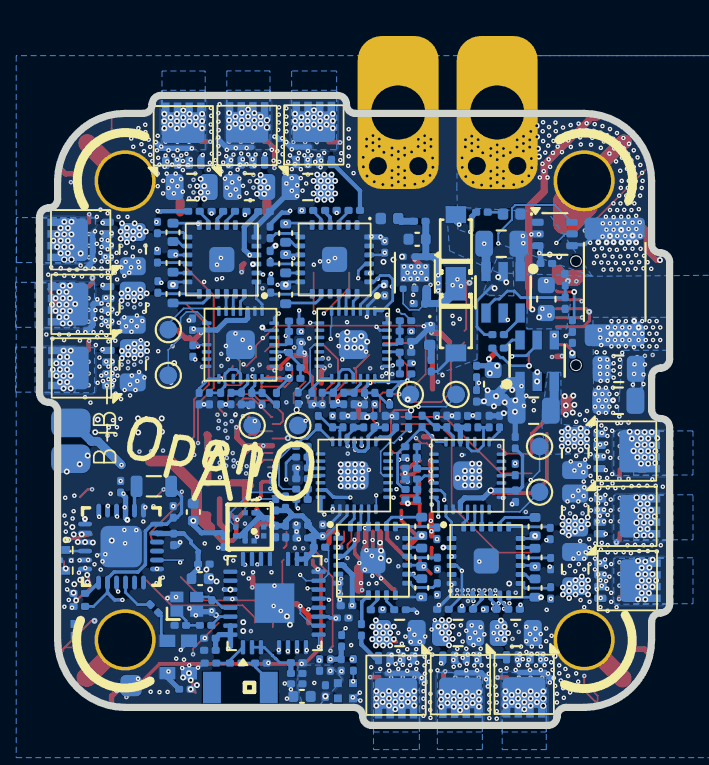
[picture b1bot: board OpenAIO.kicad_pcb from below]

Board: 8 copper layers, 35.0 x 35.0 mm, 343 parts (225 on the bottom side), 235 nets.

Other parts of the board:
R54, R74: 15R; R_0201_0603Metric
R59: 10R; R_0201_0603Metric
R76: 10k; R_0201_0603Metric

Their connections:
+3.3V: R59.2; also elsewhere on the board
/ESC2/GHA: R54.1; also elsewhere on the board
/ESC2/vdda: R59.1; also elsewhere on the board
/ESC3/GLA: R74.1; also elsewhere on the board
GND: R76.2; also elsewhere on the board
unnamed 154: R54.2; also elsewhere on the board
unnamed 161: R74.2; also elsewhere on the board
unnamed 204: R76.1; also elsewhere on the board
